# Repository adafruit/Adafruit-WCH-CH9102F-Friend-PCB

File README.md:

## Adafruit WCH CH9102F Friend - USB to Serial Converter PCB

<a href="http://www.adafruit.com/products/5568"><br/>
Click here to purchase one from the Adafruit shop</a>

PCB files for the Adafruit WCH CH9102F Friend - USB to Serial Converter. 

Format is EagleCAD schematic and board layout
* https://www.adafruit.com/product/5568

### Description

Long gone are the days of parallel ports and serial ports. Now the USB port reigns supreme! But USB is hard, and you just want to transfer your everyday serial data from a microcontroller to computer. What now? Enter the Adafruit CH9102F Friend, a version of our popular USB-Serial 'friend' breakouts that uses the affordable (and available) CH9102F - a 'near pin-compatible' to the CP2102N.

This board features the CH9102F USB-Serial chip that can upload code at  3Mbit/s for fast development time. It also has auto-reset for Arduino/ATmega328 boards so no noodling with pins and reset button pressings. The CH9102F has fairly good driver support, and for 99% of use cases is a fine replacement of the FTR232, FT231x or CP210x series. With a modern USB Type C connector, it's ready to rock on any kind of computer.

Some things we've noted as we have been working with this board:

The RX LED blinks as you expect when data is received, however the TX LED does not blink constantly. Instead after a few seconds of data transmission the LED will blink slowly.
On Linux, the CTS pin is not supported by the built in Linux kernel driver. Oddly enough, all the other flow control pins work perfectly fine - its just CTS that doesn't. You can fix it by installing an out-of-tree driver which we did on a Raspberry Pi. Fortunately, for uploading code to microcontrollers, almost all of them use RTS/DTR for auto-resetting so not having CTS isn't a big deal.
By default, we've set it up so that it matches our FTDI cables. The 6th pin is RTS, the power wire is +5V, and the signal levels are 3.3V (they are 5V compliant and should work in the vast majority of 3.3V and 5V signal systems). Works excellently with any Arduino, ESP8266, ESP32, or any other microcontroller that uses an 'FTDI port' for communications and upload. You can also purchase a 6-pin extension cable from us, which will let you rearrange the wire order.

There's also a full collection of all the modem control pins you may need on the side, in case you need the DTR, RI, DSR, etc. pins.

Each order comes with a fully assembled and tested board. We give you a right-angle socket header and some male header strip. You can solder in the socket header on the edge to make it 'FTDI-like' or solder the male headers in to plug it into a breadboard and get access to all the pins.

For Linux, you won't need a driver (unless you happen to need CTS support, see above).

For Windows and MacOS X, check our tutorial page on how to install drivers.

### License

Adafruit invests time and resources providing this open source design, please support Adafruit and open-source hardware by purchasing products from [Adafruit](https://www.adafruit.com)!

Designed by Limor Fried/Ladyada for Adafruit Industries.

Creative Commons Attribution/Share-Alike, all text above must be included in any redistribution. 
See license.txt for additional details.

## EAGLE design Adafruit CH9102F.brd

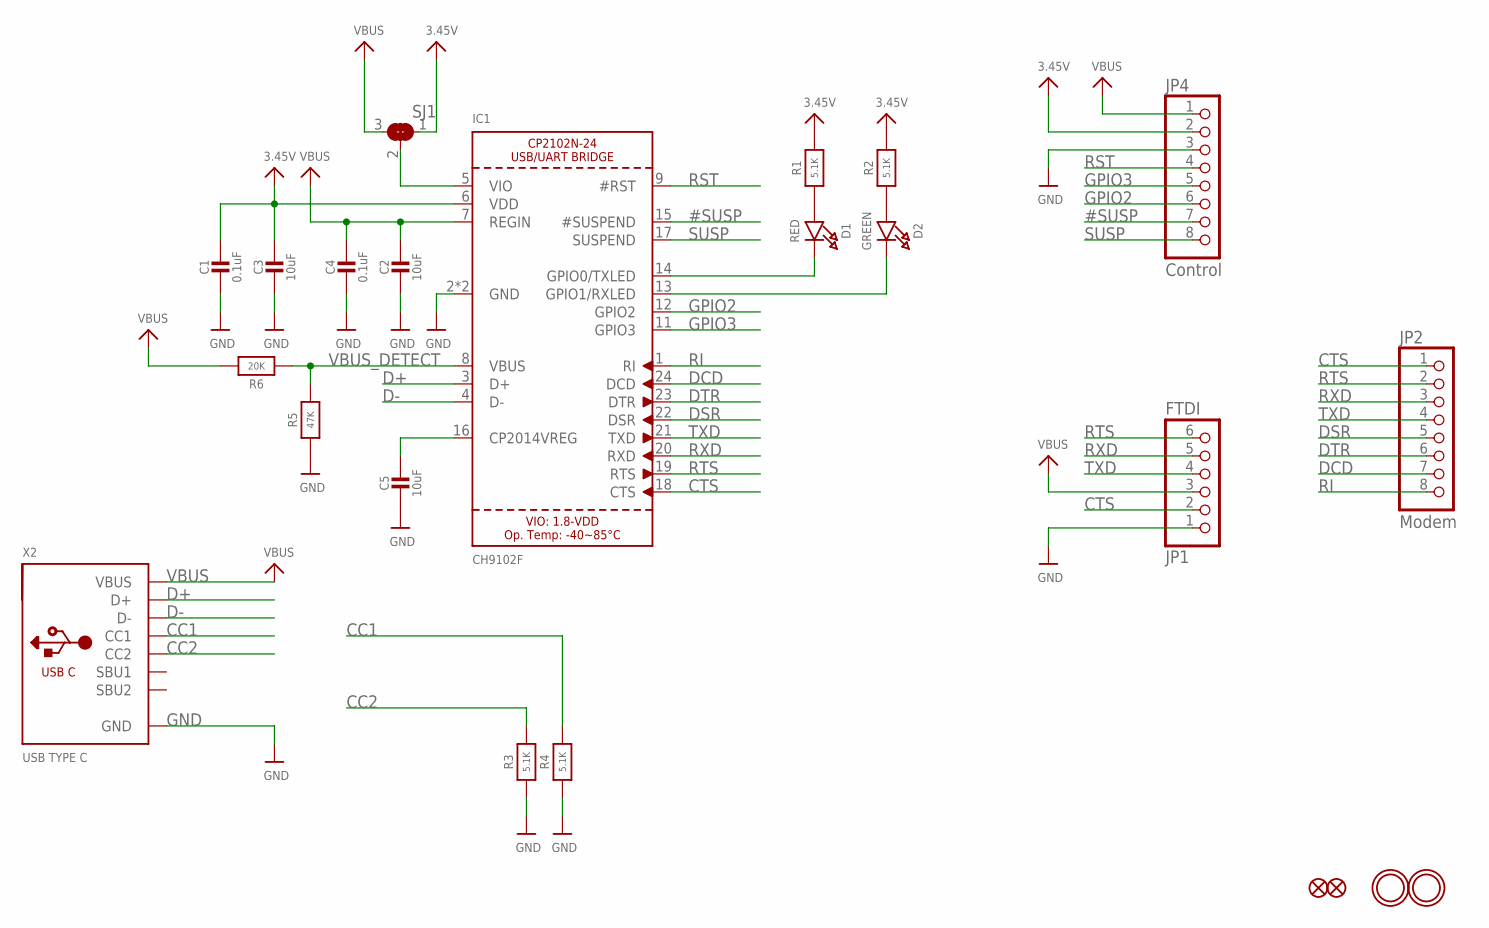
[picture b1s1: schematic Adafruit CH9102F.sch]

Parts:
C1, C4: 0.1uF; 0603-NO
C2, C3, C5: 10uF; 0805-NO
D1: RED; CHIPLED_0603_NOOUTLINE
D2: GREEN; CHIPLED_0603_NOOUTLINE
FID1, FID2: FIDUCIAL_1MM
IC1: CH9102F; QFN24_4MM_SMSC
JP1: FTDI; 1X06_ROUND_76
JP2: Modem; 1X08_ROUND_70
JP4: Control; 1X08_ROUND_70
R1, R2, R3, R4: 5.1K; 0603-NO
R5: 47K; 0603-NO
R6: 20K; 0603-NO
SJ1: SOLDERJUMPER_2WAY; SOLDERJUMPER_2WAY_OPEN_NOPASTE
U$18, U$19: MOUNTINGHOLE2.5; MOUNTINGHOLE_2.5_PLATED
X2: USB TYPE C; USB_C_CUSB31-CFM2AX-01-X

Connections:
3.3V: C1.1, C3.1, IC1.6 (VDD), JP4.2, R1.2, R2.2, SJ1.1
#SUSP: IC1.15 (#SUSPEND), JP4.7
CC1: R4.2, X2.A5 (CC1)
CC2: R3.2, X2.B5 (CC2)
CTS: IC1.18 (CTS), JP1.2, JP2.1
D+: IC1.3 (D+), X2.A6 (D+), X2.B6 (D+)
D-: IC1.4 (D-), X2.A7 (D-), X2.B7 (D-)
DCD: IC1.24 (DCD), JP2.7
DSR: IC1.22 (DSR), JP2.5
DTR: IC1.23 (DTR), JP2.6
GND: C1.2, C2.2, C3.2, C4.2, C5.2, IC1.2 (GND), IC1.THERM (GND), JP1.1, JP4.3, R3.1, R4.1, R5.1, X2.A1B12 (GND), X2.B1A12 (GND)
GPIO2: IC1.12 (GPIO2), JP4.6
GPIO3: IC1.11 (GPIO3), JP4.5
unnamed: D1.A, R1.1
unnamed: C5.1, IC1.16 (CP2014VREG)
unnamed: IC1.5 (VIO), SJ1.2
unnamed: D2.A, R2.1
unnamed: D1.C, IC1.14 (GPIO0/TXLED)
unnamed: D2.C, IC1.13 (GPIO1/RXLED)
RI: IC1.1 (RI), JP2.8
RST: IC1.9 (#RST), JP4.4
RTS: IC1.19 (RTS), JP1.6, JP2.2
RXD: IC1.20 (RXD), JP1.5, JP2.3
SUSP: IC1.17 (SUSPEND), JP4.8
TXD: IC1.21 (TXD), JP1.4, JP2.4
VBUS: C2.1, C4.1, IC1.7 (REGIN), JP1.3, JP4.1, R6.2, SJ1.3, X2.A4B9 (VBUS), X2.B4A9 (VBUS)
VBUS_DETECT: IC1.8 (VBUS), R5.2, R6.1

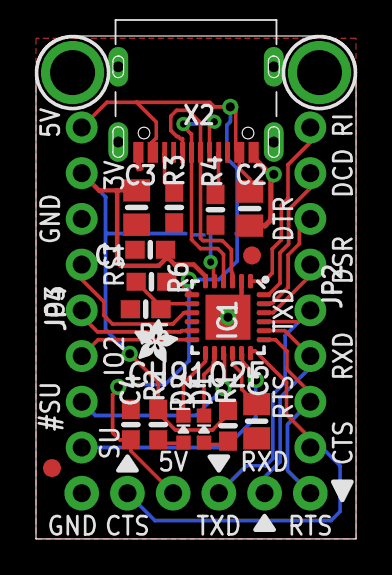
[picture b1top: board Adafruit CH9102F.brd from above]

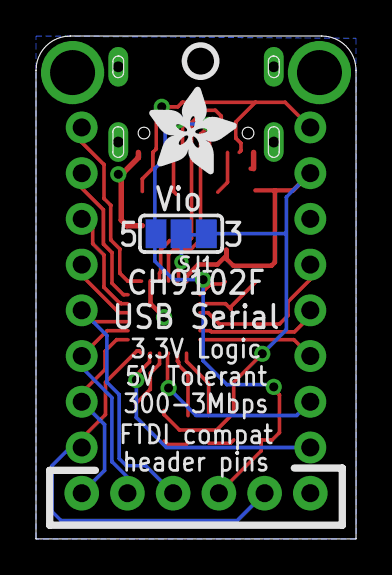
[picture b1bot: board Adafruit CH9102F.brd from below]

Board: 2 copper layers, 17.8 x 27.9 mm, 26 parts (3 on the bottom side), 27 nets.

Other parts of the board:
U$8: ADAFRUIT_2.5MM
U$17: PCBFEAT-REV-040
U$22: ADAFRUIT_5MM

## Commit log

2022-09-22 Adding cookiecutter output
2022-09-22 updating readme

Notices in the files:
parts and their libraries:
microbuilder: This work is placed in the public domain, and may be freely used for commercial and non-commercial work with the following conditions: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
